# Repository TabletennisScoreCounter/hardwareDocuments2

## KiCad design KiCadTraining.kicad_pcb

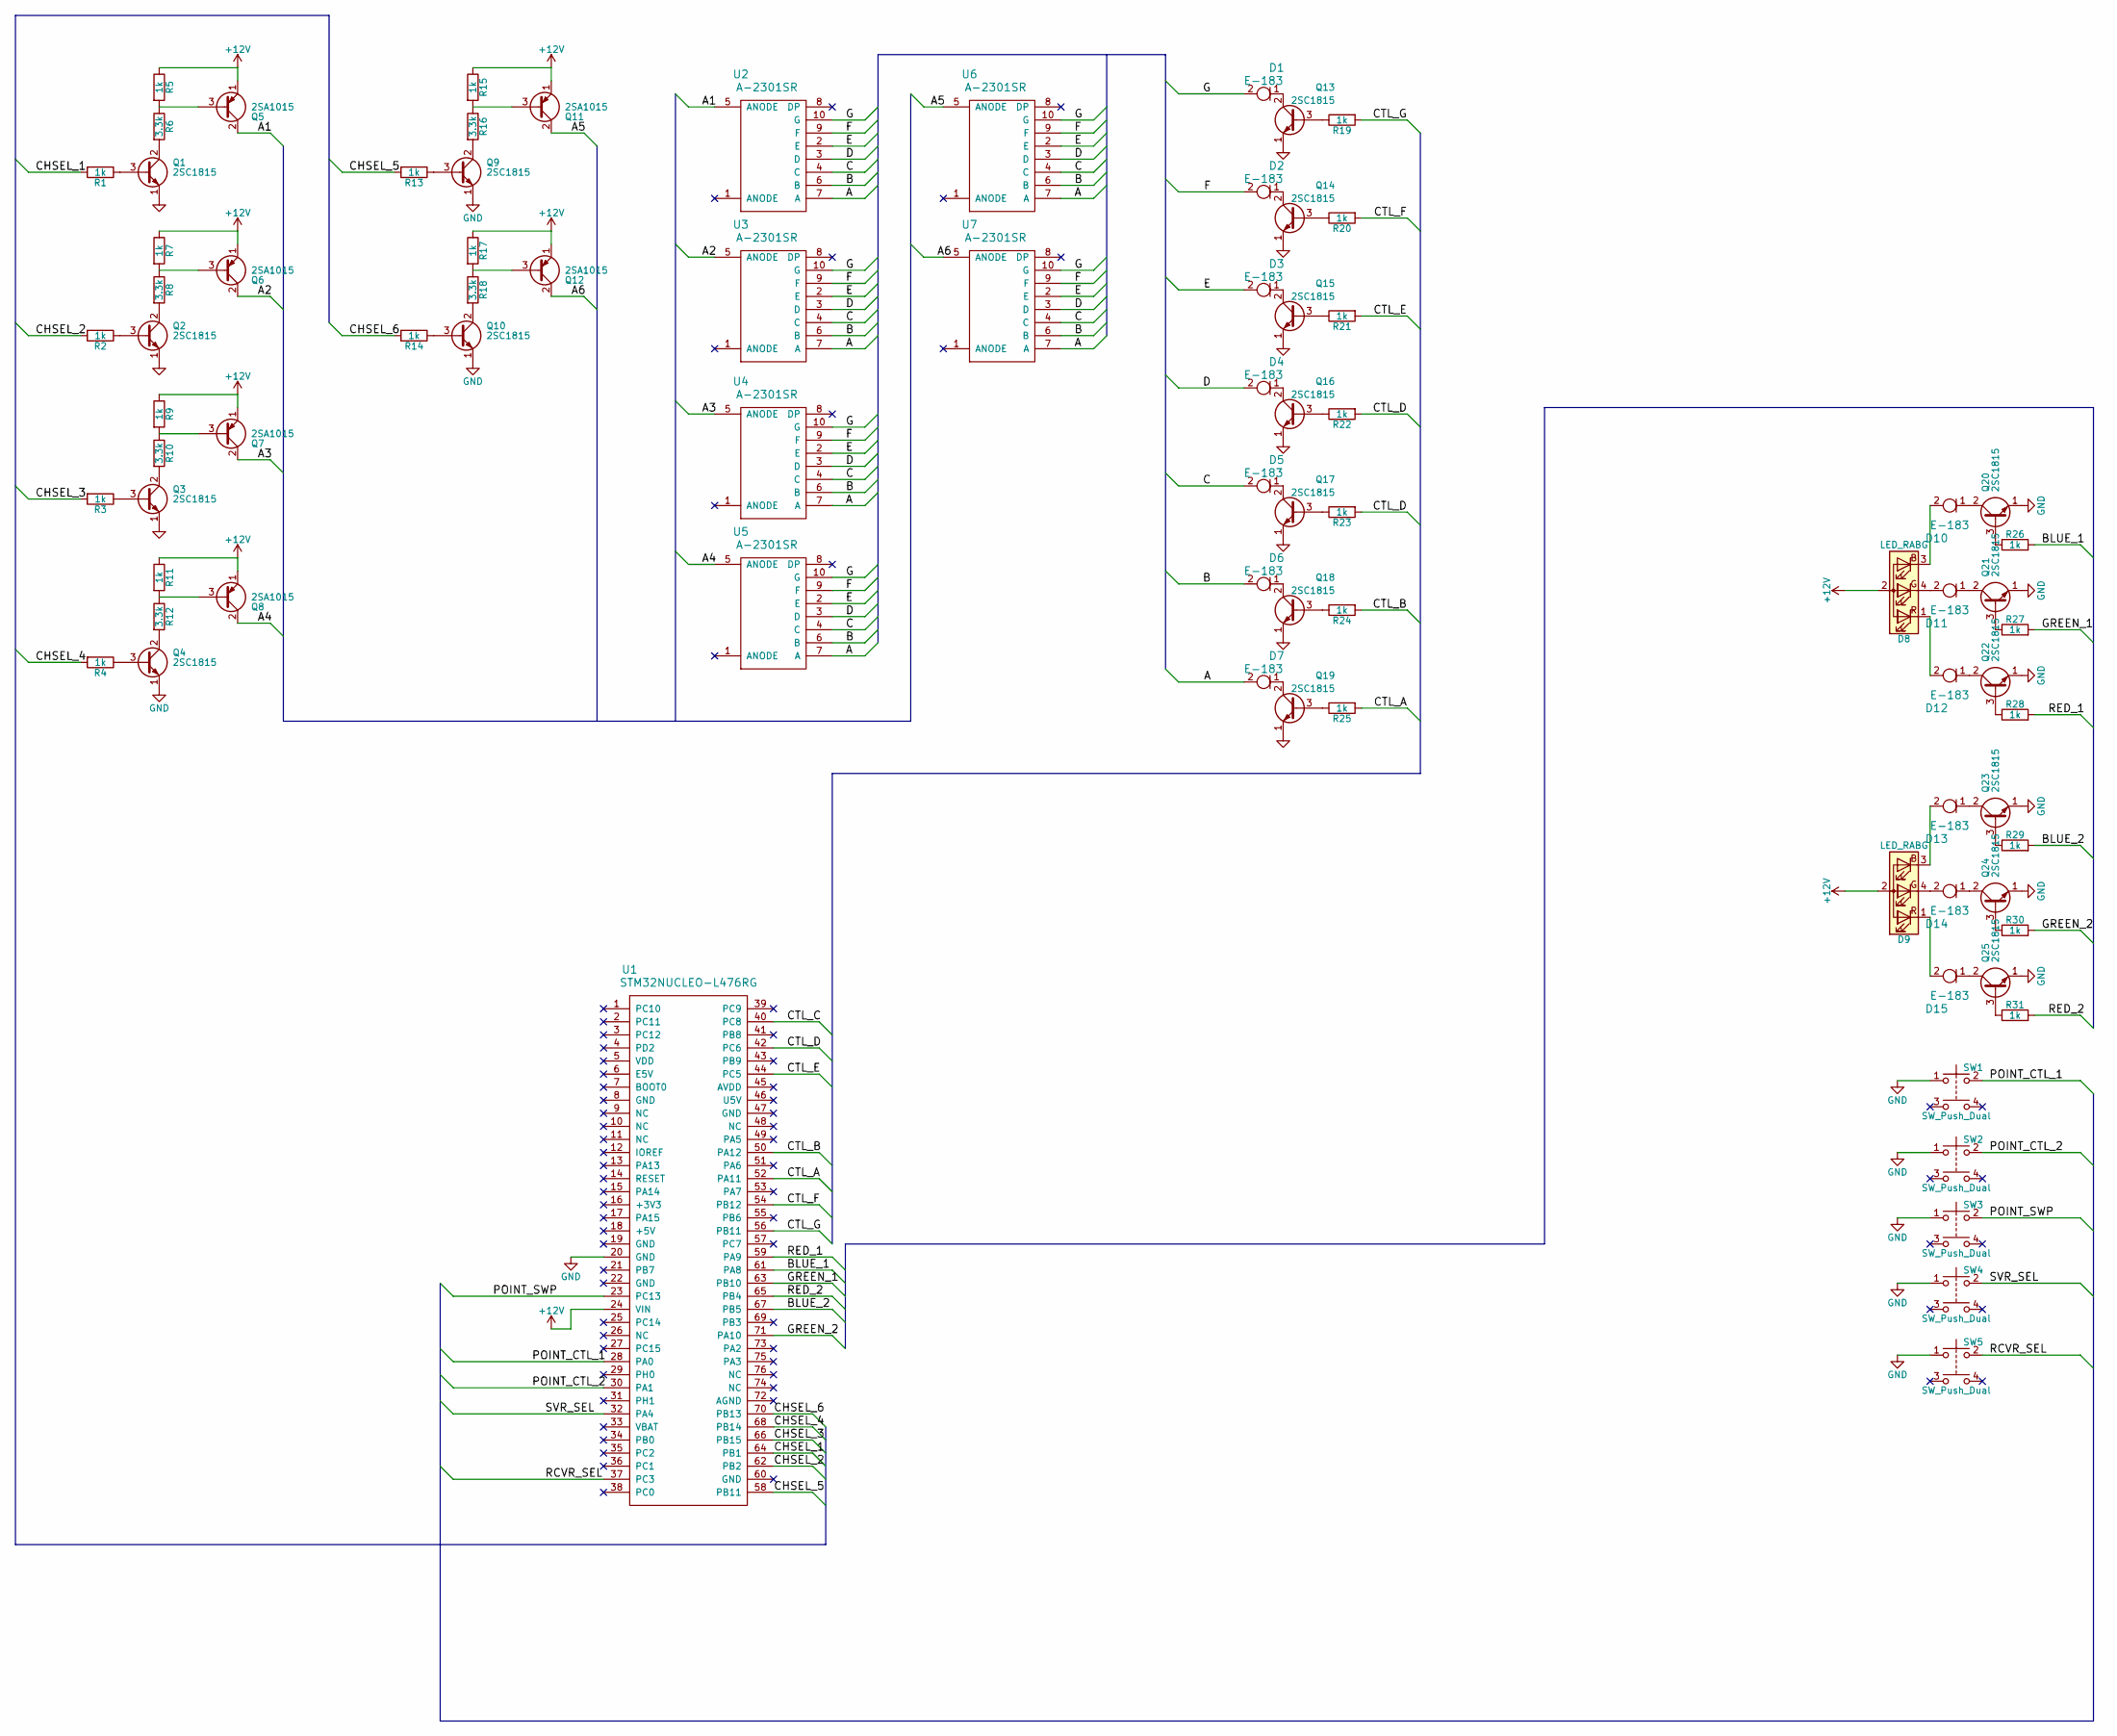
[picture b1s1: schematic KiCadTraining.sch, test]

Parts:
D1, D2, D3, D4, D5, D6, D7, D10, D11, D12, D13, D14, D15: E-183; D_T-1_P10.16mm_Horizontal
D8, D9: LED_RABG; LED_D5.0mm-4
Q1, Q2, Q3, Q4, Q9, Q10, Q13, Q14, Q15, Q16, Q17, Q18, Q19, Q20, Q21, Q22, Q23, Q24, Q25: 2SC1815; TO-92_Inline_Wide
Q5, Q6, Q7, Q8, Q11, Q12: 2SA1015; TO-92_Inline_Wide
R1, R2, R3, R4, R5, R7, R9, R11, R13, R14, R15, R17, R19, R20, R21, R22, R23, R24, R25, R26, R27, R28, R29, R30, R31: 1k; R_Axial_DIN0309_L9.0mm_D3.2mm_P12.70mm_Horizontal
R6, R8, R10, R12, R16, R18: 3.3k; R_Axial_DIN0309_L9.0mm_D3.2mm_P12.70mm_Horizontal
SW1, SW2, SW3, SW4, SW5: SW_Push_Dual; SW_TH_Tactile_Omron_B3F-10xx
U1: STM32NUCLEO-L476RG; STM32L476NUCLEO
U2, U3, U4, U5, U6, U7: A-2301SR

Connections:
+12V: D8.2 (A), D9.2 (A), Q5.1 (E), Q6.1 (E), Q7.1 (E), Q8.1 (E), Q11.1 (E), Q12.1 (E), R5.1, R7.1, R9.1, R11.1, R15.1, R17.1, U1.24 (VIN)
/A: D7.2, U2.7 (A), U3.7 (A), U4.7 (A), U5.7 (A), U6.7 (A), U7.7 (A)
/A1: Q5.2 (C), U2.5 (ANODE)
/A2: Q6.2 (C), U3.5 (ANODE)
/A3: Q7.2 (C), U4.5 (ANODE)
/A4: Q8.2 (C), U5.5 (ANODE)
/A5: Q11.2 (C), U6.5 (ANODE)
/A6: Q12.2 (C), U7.5 (ANODE)
/B: D6.2, U2.6 (B), U3.6 (B), U4.6 (B), U5.6 (B), U6.6 (B), U7.6 (B)
/BLUE_1: R26.2, U1.61 (PA8)
/BLUE_2: R29.2, U1.67 (PB5)
/C: D5.2, U2.4 (C), U3.4 (C), U4.4 (C), U5.4 (C), U6.4 (C), U7.4 (C)
/CHSEL_1: R1.2, U1.64 (PB1)
/CHSEL_2: R2.2, U1.62 (PB2)
/CHSEL_3: R3.2, U1.66 (PB15)
/CHSEL_4: R4.2, U1.68 (PB14)
/CHSEL_5: R13.2, U1.58 (PB11)
/CHSEL_6: R14.2, U1.70 (PB13)
/CTL_A: R25.2, U1.52 (PA11)
/CTL_B: R24.2, U1.50 (PA12)
/CTL_C: U1.40 (PC8)
/CTL_D: R22.2, R23.2, U1.42 (PC6)
/CTL_E: R21.2, U1.44 (PC5)
/CTL_F: R20.2, U1.54 (PB12)
/CTL_G: R19.2, U1.56 (PB11)
/D: D4.2, U2.3 (D), U3.3 (D), U4.3 (D), U5.3 (D), U6.3 (D), U7.3 (D)
/E: D3.2, U2.2 (E), U3.2 (E), U4.2 (E), U5.2 (E), U6.2 (E), U7.2 (E)
/F: D2.2, U2.9 (F), U3.9 (F), U4.9 (F), U5.9 (F), U6.9 (F), U7.9 (F)
/G: D1.2, U2.10 (G), U3.10 (G), U4.10 (G), U5.10 (G), U6.10 (G), U7.10 (G)
/GREEN_1: R27.2, U1.63 (PB10)
/GREEN_2: R30.2, U1.71 (PA10)
/POINT_CTL_1: SW1.2, U1.28 (PA0)
/POINT_CTL_2: SW2.2, U1.30 (PA1)
/POINT_SWP: SW3.2, U1.23 (PC13)
/RCVR_SEL: SW5.2, U1.37 (PC3)
/RED_1: R28.2, U1.59 (PA9)
/RED_2: R31.2, U1.65 (PB4)
/SVR_SEL: SW4.2, U1.32 (PA4)
GND: Q1.1 (E), Q2.1 (E), Q3.1 (E), Q4.1 (E), Q9.1 (E), Q10.1 (E), Q13.1 (E), Q14.1 (E), Q15.1 (E), Q16.1 (E), Q17.1 (E), Q18.1 (E), Q19.1 (E), Q20.1 (E), Q21.1 (E), Q22.1 (E), Q23.1 (E), Q24.1 (E), Q25.1 (E), SW1.1, SW2.1, SW3.1, SW4.1, SW5.1, U1.20 (GND)
unnamed: D1.1, Q13.2 (C)
unnamed: D2.1, Q14.2 (C)
unnamed: D3.1, Q15.2 (C)
unnamed: D4.1, Q16.2 (C)
unnamed: D5.1, Q17.2 (C)
unnamed: D6.1, Q18.2 (C)
unnamed: D7.1, Q19.2 (C)
unnamed: D10.1, Q20.2 (C)
unnamed: D8.3 (BK), D10.2
unnamed: D11.1, Q21.2 (C)
unnamed: D8.4 (GK), D11.2
unnamed: D12.1, Q22.2 (C)
unnamed: D8.1 (RK), D12.2
unnamed: D13.1, Q23.2 (C)
unnamed: D9.3 (BK), D13.2
unnamed: D14.1, Q24.2 (C)
unnamed: D9.4 (GK), D14.2
unnamed: D15.1, Q25.2 (C)
unnamed: D9.1 (RK), D15.2
unnamed: Q1.2 (C), R6.2
unnamed: Q1.3 (B), R1.1
unnamed: Q2.2 (C), R8.2
unnamed: Q2.3 (B), R2.1
unnamed: Q3.2 (C), R10.2
unnamed: Q3.3 (B), R3.1
unnamed: Q4.2 (C), R12.2
unnamed: Q4.3 (B), R4.1
unnamed: Q5.3 (B), R5.2, R6.1
unnamed: Q6.3 (B), R7.2, R8.1
unnamed: Q7.3 (B), R9.2, R10.1
unnamed: Q8.3 (B), R11.2, R12.1
unnamed: Q9.2 (C), R16.2
unnamed: Q9.3 (B), R13.1
unnamed: Q10.2 (C), R18.2
unnamed: Q10.3 (B), R14.1
unnamed: Q11.3 (B), R15.2, R16.1
unnamed: Q12.3 (B), R17.2, R18.1
unnamed: Q13.3 (B), R19.1
unnamed: Q14.3 (B), R20.1
unnamed: Q15.3 (B), R21.1
unnamed: Q16.3 (B), R22.1
unnamed: Q17.3 (B), R23.1
unnamed: Q18.3 (B), R24.1
unnamed: Q19.3 (B), R25.1
unnamed: Q20.3 (B), R26.1
unnamed: Q21.3 (B), R27.1
unnamed: Q22.3 (B), R28.1
unnamed: Q23.3 (B), R29.1
unnamed: Q24.3 (B), R30.1
unnamed: Q25.3 (B), R31.1

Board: 2 copper layers, 83 parts (11 on the bottom side), 88 nets, no tracks yet.

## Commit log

2017-10-02 7seg配線完了 STM32追加
2017-10-03 Nucleo基板に修正 プッシュスイッチ 追加 RGB追加
2017-10-04 パッシブ部品の足を全てパッシブに変更
2017-10-12 部品レイアウト完了
2017-10-13 部品レイアウトを合理化
